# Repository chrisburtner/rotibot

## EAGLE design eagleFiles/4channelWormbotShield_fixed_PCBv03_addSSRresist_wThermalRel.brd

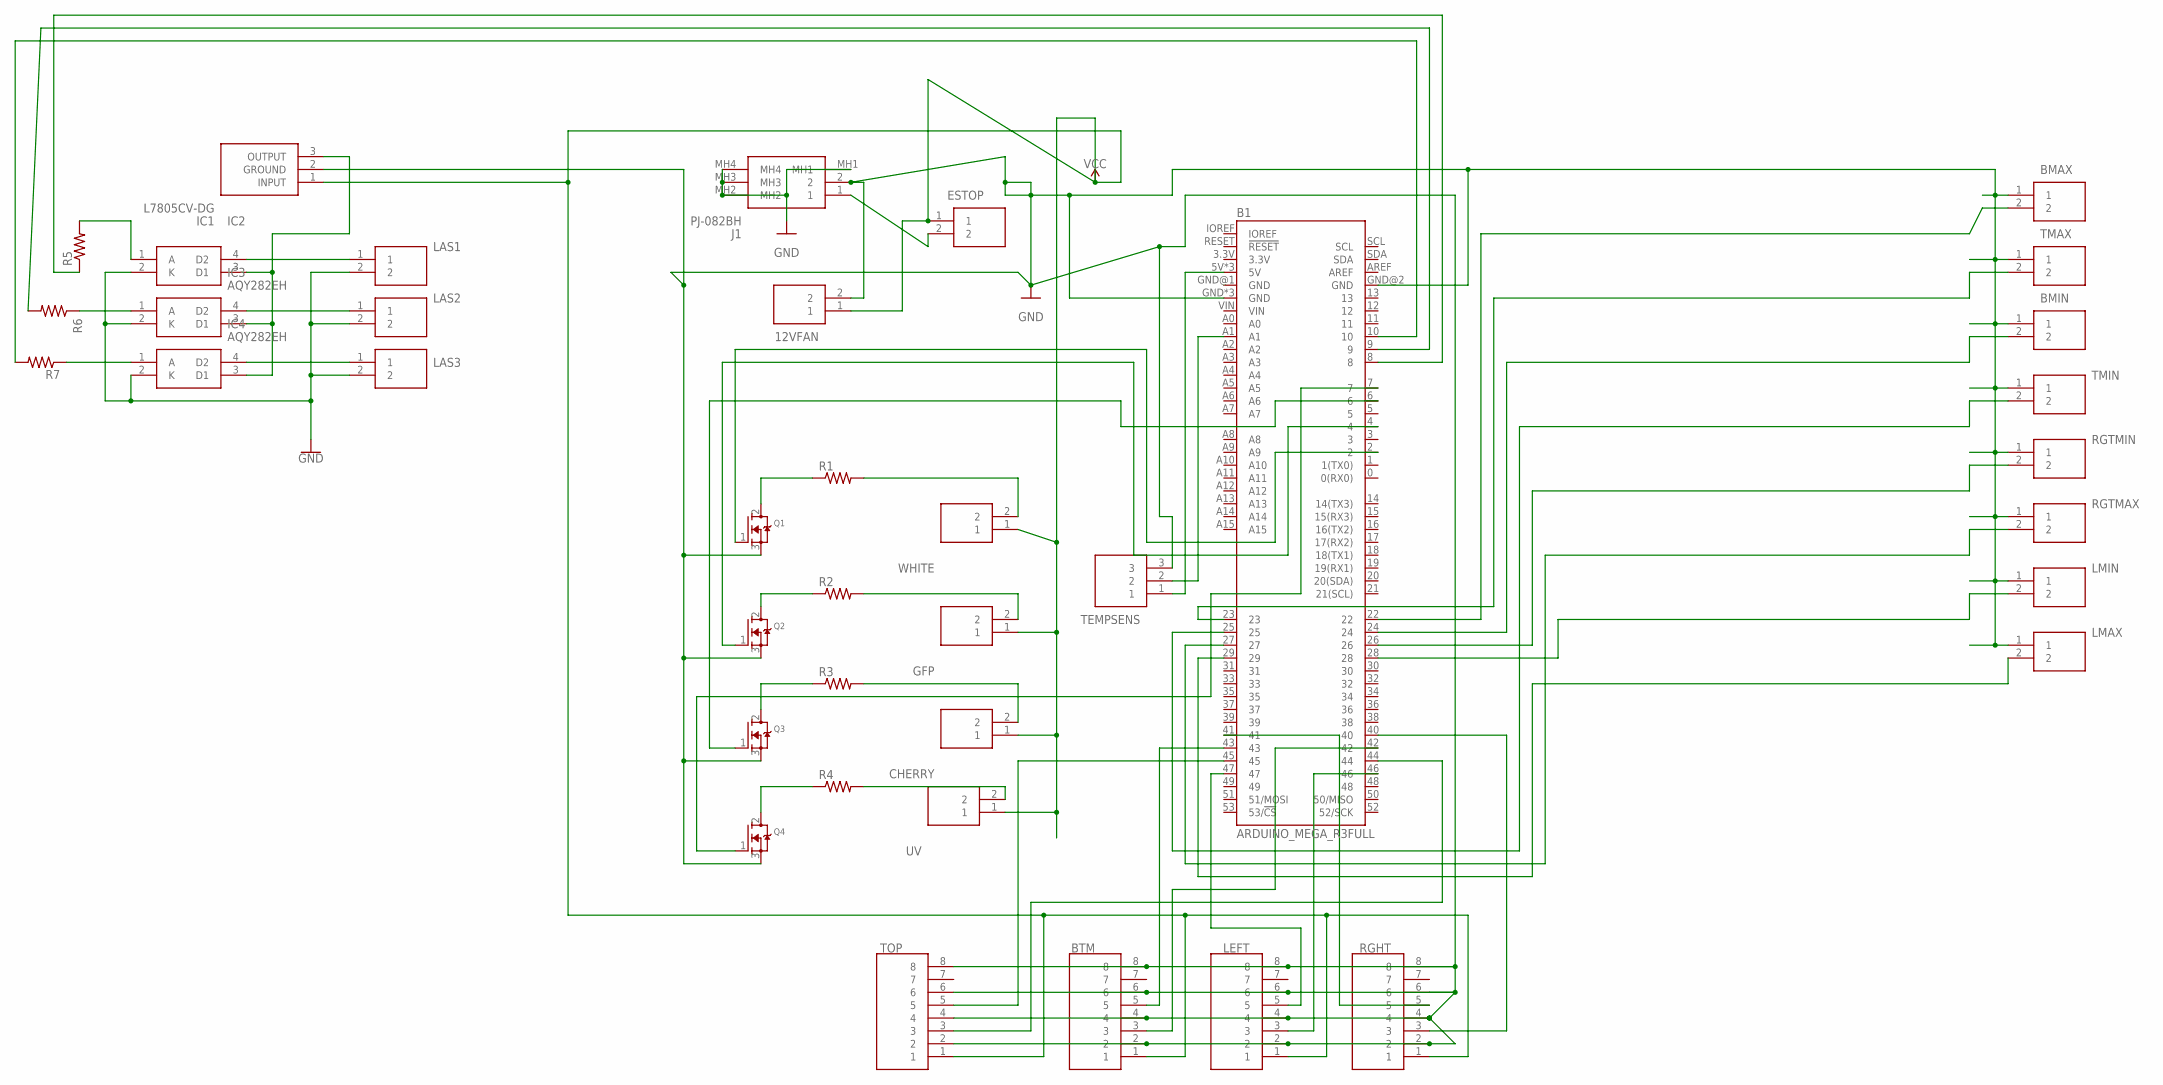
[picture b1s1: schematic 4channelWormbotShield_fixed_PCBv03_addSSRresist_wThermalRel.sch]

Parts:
12VFAN: 1725656
B1: ARDUINO_MEGA_R3FULL; ARDUINO_MEGA_NO_SILK
BMAX: 1725656
BMIN: 1725656
BTM: 1725711
CHERRY: 1725656
ESTOP: TB003-500-P02BE; SHDR2W100P0X500_1X2_1000X780X1
GFP: 1725656
IC1: L7805CV-DG; TO255P460X1020X2008-3P
IC2, IC3, IC4: AQY282EH; DIP762W57P254L478H340Q4N
J1: PJ-082BH; PJ082BH
LAS1, LAS2, LAS3: 1725656
LEFT: 1725711
LMAX: 1725656
LMIN: 1725656
Q1, Q2, Q3, Q4: MOSFET-NGDS_TO220V; TO220V
R1, R2, R3, R4, R5, R6, R7: R-US_0207/10; 0207/10
RGHT: 1725711
RGTMAX: 1725656
RGTMIN: 1725656
TEMPSENS: 1725669
TMAX: 1725656
TMIN: 1725656
TOP: 1725711
UV: 1725656
WHITE: 1725656

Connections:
GND: 12VFAN.2, B1.GND, B1.GND@2 (GND), B1.GND@3 (GND), B1.GND@4 (GND), BMAX.1, BMIN.1, BTM.2, BTM.4, BTM.6, BTM.8, IC1.2 (GROUND), IC2.2 (K), IC3.2 (K), IC4.2 (K), J1.2, J1.MH1, J1.MH2, J1.MH3, J1.MH4, LAS1.2, LAS2.2, LAS3.2, LEFT.2, LEFT.4, LEFT.6, LEFT.8, LMAX.1, LMIN.1, Q1.3 (S), Q2.3 (S), Q3.3 (S), Q4.3 (S), RGHT.2, RGHT.4, RGHT.6, RGHT.8, RGTMAX.1, RGTMIN.1, TEMPSENS.3, TMAX.1, TMIN.1, TOP.2, TOP.4, TOP.6, TOP.8
unnamed: B1.22, BMAX.2
unnamed: B1.23, TMAX.2
unnamed: B1.24, BMIN.2
unnamed: R1.2, WHITE.2
unnamed: GFP.2, R2.2
unnamed: CHERRY.2, R3.2
unnamed: B1.25, TMIN.2
unnamed: B1.2, Q1.1 (G)
unnamed: B1.4, Q2.1 (G)
unnamed: B1.6, Q3.1 (G)
unnamed: B1.27, RGTMAX.2
unnamed: B1.26, RGTMIN.2
unnamed: B1.28, LMIN.2
unnamed: B1.29, LMAX.2
unnamed: B1.44, TOP.3
unnamed: B1.45, TOP.5
unnamed: B1.42, BTM.3
unnamed: B1.43, BTM.5
unnamed: B1.46, LEFT.3
unnamed: B1.47, LEFT.5
unnamed: B1.40, RGHT.3
unnamed: B1.41, RGHT.5
unnamed: R4.2, UV.2
unnamed: B1.5V, B1.5V@1 (5V), B1.5V@2 (5V), TEMPSENS.1
unnamed: IC2.1 (A), R5.2
unnamed: B1.A1, TEMPSENS.2
unnamed: ESTOP.2, J1.1
unnamed: IC2.4 (D2), LAS1.1
unnamed: IC3.4 (D2), LAS2.1
unnamed: B1.8, R5.1
unnamed: IC4.4 (D2), LAS3.1
unnamed: IC1.3 (OUTPUT), IC2.3 (D1), IC3.3 (D1), IC4.3 (D1)
unnamed: B1.9, R6.2
unnamed: B1.10, R7.2
unnamed: Q1.2 (D), R1.1
unnamed: Q2.2 (D), R2.1
unnamed: Q3.2 (D), R3.1
unnamed: Q4.2 (D), R4.1
unnamed: B1.7, Q4.1 (G)
unnamed: IC3.1 (A), R6.1
unnamed: IC4.1 (A), R7.1
VCC: 12VFAN.1, BTM.1, CHERRY.1, ESTOP.1, GFP.1, IC1.1 (INPUT), LEFT.1, RGHT.1, TOP.1, UV.1, WHITE.1

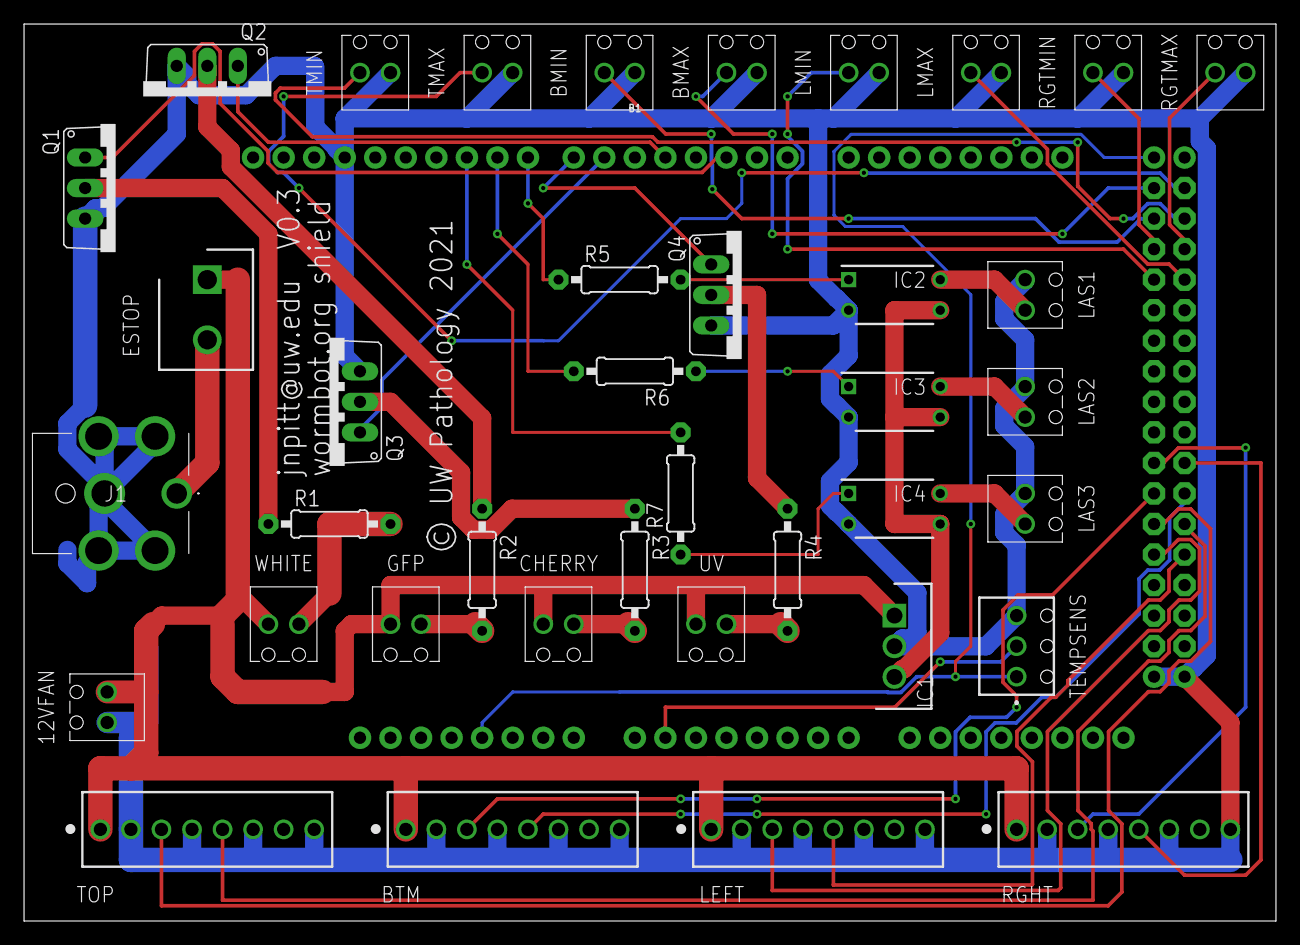
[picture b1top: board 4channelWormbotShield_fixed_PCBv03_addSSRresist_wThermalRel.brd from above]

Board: 2 copper layers, 104.1 x 74.6 mm, 39 parts (0 on the bottom side), 43 nets.

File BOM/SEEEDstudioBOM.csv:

Designator,MPN,Qty,Link
"12VFAN,BMAX,BMIN,CHERRY,GFP,LAS1,LAS2,LAS3,LMAX,LMIN,RGTMAX,RGTMIN,TMAX,TMIN,UV,WHITE",B2B-XH-A(LF)(SN),16,https://www.digikey.com/en/products/detail/jst-sales-america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
"BOT,LEFT,RIGHT,TOP",B8B-XH-A(LF)(SN),4,https://www.digikey.com/en/products/detail/jst-sales-america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
TEMPSENS,B3B-XH-A(LF)(SN),1,https://www.digikey.com/en/products/detail/jst-sales-america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
ARDUINO_MEGA_R3FULL,9-146281-0,1,https://www.mouser.com/ProductDetail/TE-Connectivity/9-14628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
ESTOP,TB003-500-P02BE,1,https://www.digikey.com/en/products/detail/cui-devices/TB003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
IC1,L7805CV-DG,1,https://www.digikey.com/en/products/detail/stmicroelectronic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
"IC2,IC3,IC4",AQY282EH,3,https://www.digikey.com/en/products/detail/panasonic-electri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
J1,PJ-082BH,1,https://www.digikey.com/en/products/detail/cui-devices/PJ-08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
"Q1,Q2,Q3,Q4",IRFZ44NPBF,4,https://www.mouser.com/ProductDetail/Infineon-IR/IRFZ44NPBF?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
R1,MBA02040Z0000ZRP00,1,https://www.mouser.com/ProductDetail/Vishay-BC-Components/MB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
"R2,R3,R4",RSF100JT-73-100R,3,https://www.mouser.com/ProductDetail/YAGEO/RSF100JT-73-100R?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
"R5,R6,R7",PR01000102201JR500,3,https://www.mouser.com/ProductDetail/Vishay-BC-Components/PR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
,,,
to help with construction,A000067,1,https://www.digikey.com/en/products/detail/arduino/A000067/2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

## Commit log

2020-07-09 branch from wormbotmini
2020-07-15 sent to yale status
2020-07-15 adding pause onloading to wait for serial handshake following hardware zero
2020-08-05 updated makefile, added logging to retrograde uploads
2020-08-05 updated retrograde to mainbrach status
2020-08-05 fix marker bug , image tag garbled by debug output in html
2020-08-18 updated graphmaker to main branch
2020-08-18 updated CONFIG for graphmaker
2020-08-19 updated UPDATE script, set scan time to 20 minutes
2020-08-25 forked controller to rapidscan for high frame rate timelapse
2020-08-25 tweak firmware for rapidscan
2020-08-26 added accel and decl curves to firmware
2020-09-02 updated firmware and rapidscan, NOTE motor controllers must be set to < 3 amps
2020-09-16 updated firmware, V3 now matches V1 speeds on fullsize 12plate robots, requires firmware update, NOTE ALL MOTOR CONTROLLERS SHOULD BE SET TO 3AMPS MAXIMUM
2020-11-09 added error handling for retrograde to deal with missing frames and null images
2020-11-09 adding disk space warning to controller
2020-11-12 increased sample number for temp sensors, added hard drive space monitoring to controller
2020-12-09 added daily email updates
2020-12-20 updated status frequency
2020-12-23 added mailutils library
2021-01-13 fixed debugging bug that corrupts marker img tag
2021-01-21 added offline version of retrograde
2021-02-02 updated Temp control in firmware for 1.1V voltage internal reference
2021-03-23 created moveToExternal
2021-06-30 support for 3rd color
2021-07-02 adding updated UI
2021-07-14 v2.0 software upgrade, not ready for full release
2021-07-18 fix frame increment bug
2021-08-04 added fluorescent channel controls to retrograde
2021-08-05 added channel control redraws and channel blocks
2021-09-16 added timelog
2021-09-21 added dailymonitor to timelog
2021-10-13 wormlistupdater bug fixes, retrograde upgrades, added contour channel viz
2021-12-28 updating retrograde for 3 channel fluorescence
2021-12-28 pylon drivers added
2021-12-28 fixed CONFIG bugs
2021-12-30 fixed cgiccretro bugs with new retro gui
2022-01-03 retrograde upgrade
2022-02-02 diffcalc and gen coords and wormlistupdater
2022-02-02 update retrograde for top of frame info
2022-02-03 added eagle board files for wormbot shield
2022-02-03 fixed retrograde navigation bug
2022-02-03 fixed wormlist updater retro movie data fields
2022-02-09 update toolsset for retrograde
2022-02-10 added image quantification tools to updatewormlist and retrograde
2022-02-11 update retrograde to export variable resolution movies
2022-02-15 changes to retro wormlistupdater
2022-02-16 added channel selection for retrograde lifespan and countours
2022-02-17 updated cgiccretro and retrograde to support fluorescence channels for lifespan prediction
2022-02-23 added STL files for wormbotV3 3d printed parts
2022-02-23 added frontpanelExpress files
2022-02-25 updated bulk uploader for new exposure fluor channels
2022-03-11 updated UPDATE script
2022-03-11 fixed upsupported scheduler edit bug
2022-03-11 newretro2 now retrograde, retrograde now oldretro
2022-03-11 fixed scheduler add bug
2022-03-11 default exposures to zero
2022-03-23 changes to bulkuploader to prevent improper templates from being uploaded, added file view to retrograde
2022-03-28 added getfilelist to give access to files from retrograde
2022-03-30 improved retrograde blend methods, cleaned up UI, fixed frame flashing
2022-03-30 updated retrograde index and newretro2
2022-04-04 updated estop hole size and added BOM for construction
2022-04-22 updated bulkuploader template to force column number to be correct on line 0
2022-04-22 added camera type checking for UPDATE script
2022-04-22 removed basler define from stock controller.cpp
2022-04-22 fix cross camera build config
2022-04-22 fixed makefiles
2022-06-23 changed default scan time to decrease data storage for high resolution capture
2022-10-05 added ordering list spreadsheets for V3 and mini
2022-10-07 added print set STL file for fluorescence
    for the Ender-3 Pro 3D printer
2022-10-10 added print set STL file for v3_mini
    for the Ender-3 Pro 3D printer
2022-10-10 added print set STL for v3_standard
    for the Ender-3 Pro 3D printer
2022-10-11 added print set STL file for common_parts
    for the Ender-3 Pro 3D printer
2022-10-14 fixed file path bug in getFileList
2023-03-01 updated exposure defaults and basler resolution
2023-03-01 update capture params
2023-10-06 controller.cpp
2025-08-19 Update INSTALL

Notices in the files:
eagleFiles/4channelWormbotShield_fixed_PCBv03_addSSRresist_wThermalRel.brd:
© UW Pathology 2021
parts and their libraries:
SparkFun-Boards: Licensing: Creative Commons ShareAlike 4.0 International - https://creativecommons.org/licenses/by-sa/4.0
